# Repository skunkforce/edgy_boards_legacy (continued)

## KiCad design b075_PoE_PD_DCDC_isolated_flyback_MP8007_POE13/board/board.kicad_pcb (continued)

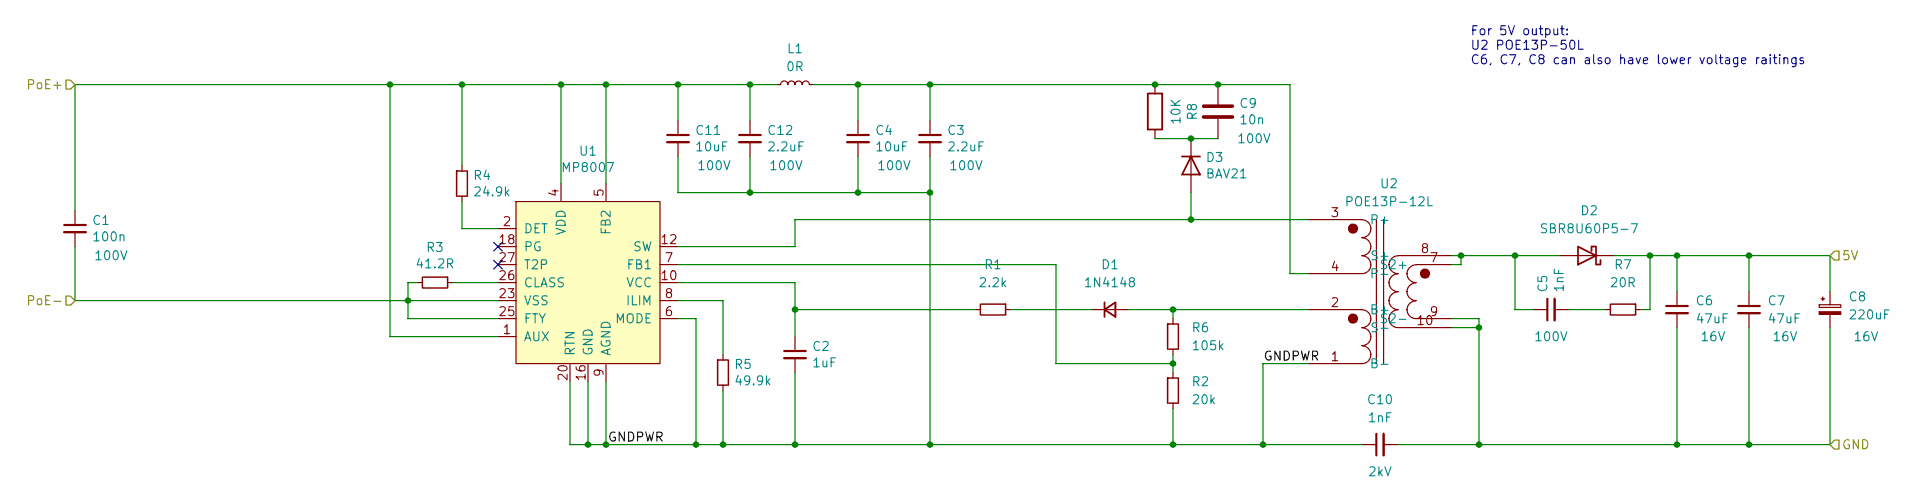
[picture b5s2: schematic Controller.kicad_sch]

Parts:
C1: 100n; C_0603_1608Metric; Voltage 100V
C2: 1uF; C_0603_1608Metric
C3, C12: 2.2uF; C_1210_3225Metric; Voltage 100V
C4, C11: 10uF; C_1210_3225Metric; Voltage 100V
C5: 1nF; C_0603_1608Metric; Voltage 100V; MPN GRM188R72A102KA01D
C6, C7: 47uF; C_1210_3225Metric; Voltage 16V
C8: 220uF; CP_Elec_10x10.5; Voltage 16V
C9: 10n; C_0805_2012Metric; Voltage 100V; MPN GRM216R72A103KA01D
C10: 1nF; C_1825_4564Metric; Voltage 2kV
D1: 1N4148; D_SOD-323; DigiKey_PN 1N4148WS_R1_00001
D2: SBR8U60P5-7; D_PowerDI-5
D3: BAV21; D_SOD-323_HandSoldering; DigiKey_PN BAV21WS_R1_00001
L1: 0R; L_1812_4532Metric
R1: 2.2k; R_0603_1608Metric
R2: 20k; R_0603_1608Metric
R3: 41.2R; R_0603_1608Metric
R4: 24.9k; R_0603_1608Metric
R5: 49.9k; R_0603_1608Metric
R6: 105k; R_0603_1608Metric
R7: 20R; R_0603_1608Metric
R8: 10K; R_1206_3216Metric
U1: MP8007; QFN-28-1EP_4x5mm_P0.5mm_EP2.65x3.65mm_ThermalVias
U2: POE13P-12L; Transformer_Coilcraft_POE13P

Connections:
/Controller/5V: C6.1, C7.1, C8.1, D2.1 (K), R7.1; also elsewhere on the board
/Controller/GNDPWR: C2.2, C3.2, C4.2, C10.1, C11.2, C12.2, R2.2, R5.2, U1.6 (MODE), U1.9 (AGND), U1.14 (NC), U1.15 (NC), U1.16 (GND), U1.17, U1.19 (NC), U1.20 (RTN), U1.21, U1.22 (NC), U1.29 (GND), U2.1 (B-)
/Controller/PoE+: C1.1, C11.1, C12.1, L1.1, R4.1, U1.1 (AUX), U1.4 (VDD), U1.5 (FB2); also elsewhere on the board
/Controller/PoE-: C1.2, R3.2, U1.23 (VSS), U1.24, U1.25 (FTY); also elsewhere on the board
GND: C6.2, C7.2, C8.2, C10.2, U2.9 (S2-), U2.10 (S-); also elsewhere on the board
unnamed: C2.1, R1.2, U1.10 (VCC)
unnamed: C3.1, C4.1, C9.1, L1.2, R8.2, U2.4 (P-)
unnamed: C5.2, R7.2
unnamed: C9.2, D3.1 (K), R8.1
unnamed: D1.1 (K), R1.1
unnamed: D1.2 (A), R6.1, U2.2 (B+)
unnamed: C5.1, D2.2 (A), U2.7 (S2+), U2.8 (S+)
unnamed: D3.2 (A), U1.12 (SW), U1.13, U2.3 (P+)
unnamed: R2.1, R6.2, U1.7 (FB1)
unnamed: R3.1, U1.26 (CLASS)
unnamed: R4.2, U1.2 (DET)
unnamed: R5.1, U1.8 (ILIM)

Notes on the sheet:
For 5V output: U2 POE13P-50L C6, C7, C8 can also have lower voltage raitings

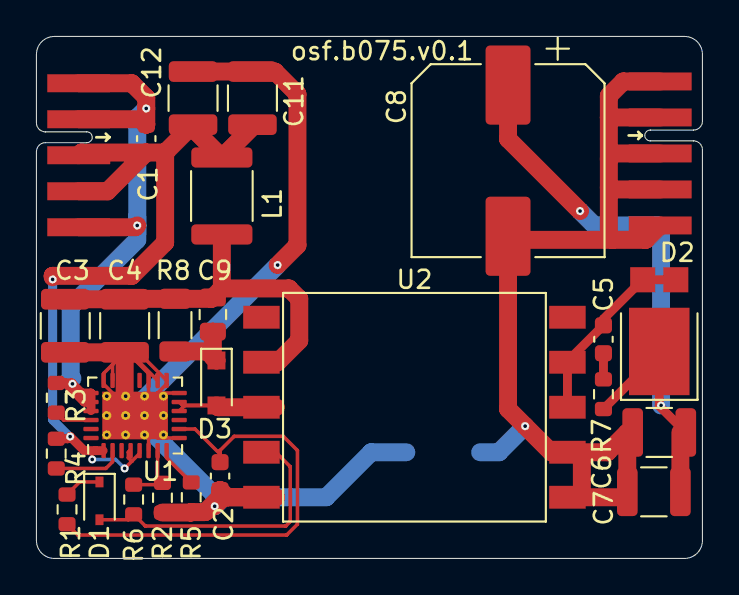
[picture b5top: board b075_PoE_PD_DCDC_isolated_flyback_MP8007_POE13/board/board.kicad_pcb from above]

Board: 2 copper layers, 37.0 x 29.0 mm, 28 parts (1 on the bottom side), 17 nets.

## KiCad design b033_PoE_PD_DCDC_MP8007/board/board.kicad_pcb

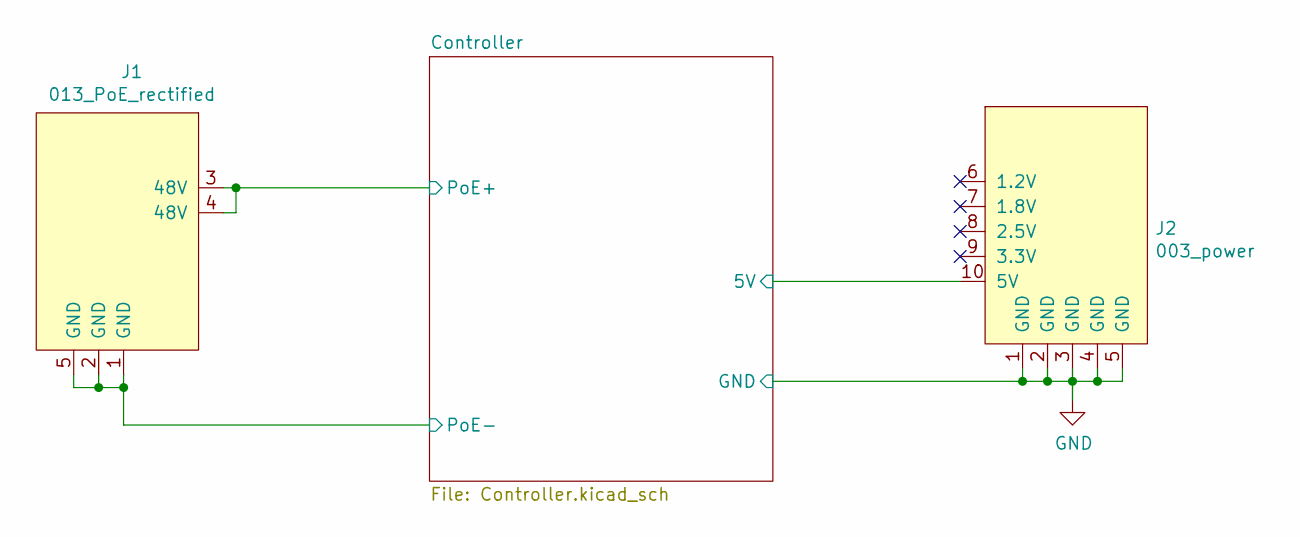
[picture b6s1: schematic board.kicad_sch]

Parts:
J1: 013_PoE_rectified; on_edge_2x05_device
J2: 003_power; on_edge_2x05_host

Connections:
/Controller/5V: J2.10 (5V); also elsewhere on the board
/Controller/PoE+: J1.3 (48V), J1.4 (48V); also elsewhere on the board
/Controller/PoE-: J1.1 (GND), J1.2 (GND), J1.5 (GND); also elsewhere on the board
GND: J2.1 (GND), J2.2 (GND), J2.3 (GND), J2.4 (GND), J2.5 (GND); also elsewhere on the board

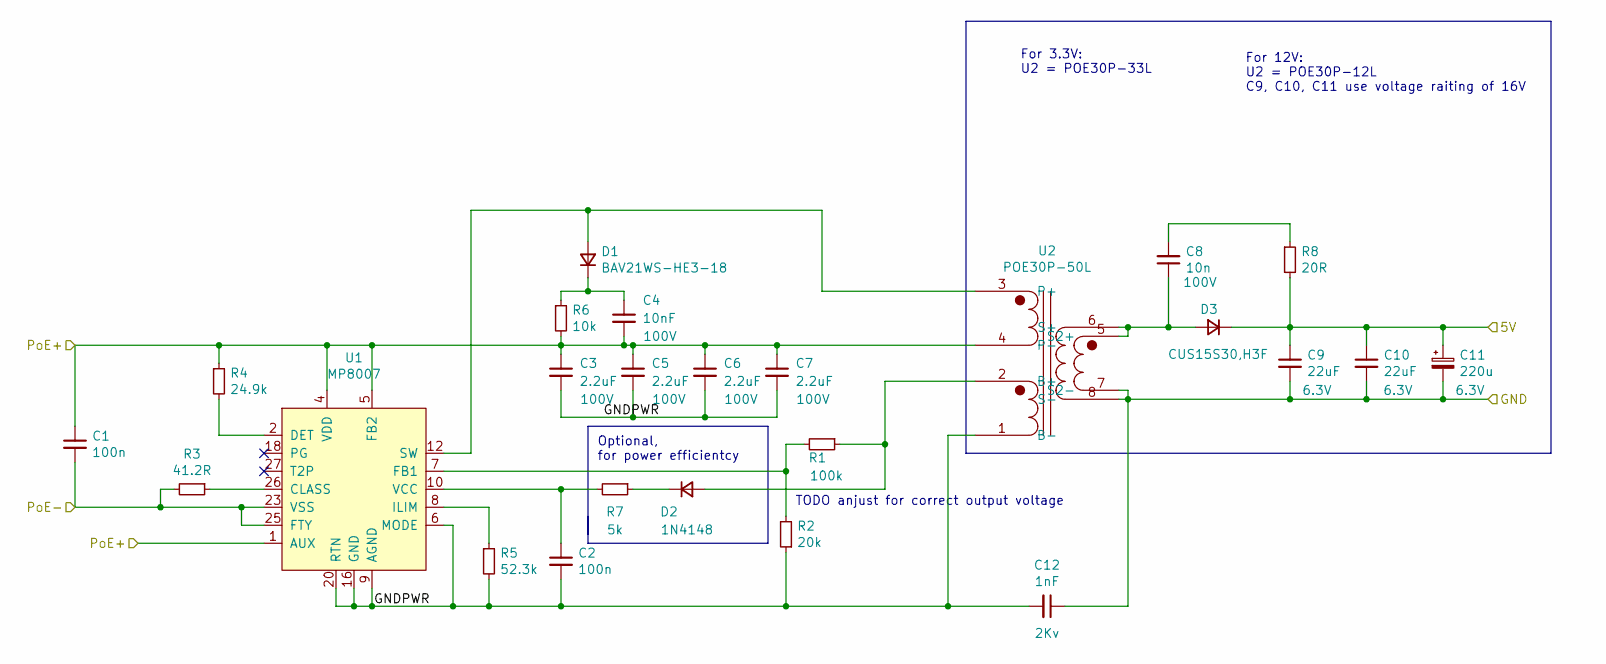
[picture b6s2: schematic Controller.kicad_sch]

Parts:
C1, C2: 100n; C_0603_1608Metric
C3, C5, C6, C7: 2.2uF; C_1210_3225Metric; Voltage 100V
C4: 10nF; C_0603_1608Metric; Voltage 100V
C8: 10n; C_0603_1608Metric; Voltage 100V
C9, C10: 22uF; C_0805_2012Metric; Voltage 6.3V
C11: 220u; CP_EIA-7343-31_Kemet-D; Voltage 6.3V
C12: 1nF; C_1806_4516Metric; Voltage 2Kv
D1: BAV21WS-HE3-18; D_SOD-323_HandSoldering
D2: 1N4148; D_SOD-323_HandSoldering
D3: CUS15S30,H3F; D_SOD-323_HandSoldering
R1: 100k; R_0603_1608Metric
R2: 20k; R_0603_1608Metric
R3: 41.2R; R_0603_1608Metric
R4: 24.9k; R_0603_1608Metric
R5: 52.3k; R_0603_1608Metric
R6: 10k; R_0603_1608Metric
R7: 5k; R_0603_1608Metric
R8: 20R; R_0603_1608Metric
U1: MP8007; QFN-28-1EP_4x5mm_P0.5mm_EP2.65x3.65mm_ThermalVias
U2: POE30P-50L; Transformer_Coilcraft_POE30P

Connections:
/Controller/5V: C9.1, C10.1, C11.1, D3.1 (K), R8.2; also elsewhere on the board
/Controller/GNDPWR: C2.2, C3.2, C5.2, C6.2, C7.2, C12.2, R2.1, R5.2, U1.6 (MODE), U1.9 (AGND), U1.16 (GND), U1.17, U1.20 (RTN), U1.21, U1.29 (GND), U2.1 (B-)
/Controller/PoE+: C1.1, C3.1, C4.2, C5.1, C6.1, C7.1, R4.1, R6.2, U1.1 (AUX), U1.4 (VDD), U1.5 (FB2), U2.4 (P-); also elsewhere on the board
/Controller/PoE-: C1.2, R3.2, U1.23 (VSS), U1.24, U1.25 (FTY); also elsewhere on the board
GND: C9.2, C10.2, C11.2, C12.1, U2.7 (S2-), U2.8 (S-); also elsewhere on the board
unnamed: C2.1, R7.2, U1.10 (VCC)
unnamed: C8.1, D3.2 (A), U2.5 (S2+), U2.6 (S+)
unnamed: C8.2, R8.1
unnamed: C4.1, D1.1 (K), R6.1
unnamed: D1.2 (A), U1.12 (SW), U1.13, U2.3 (P+)
unnamed: D2.1 (K), R7.1
unnamed: D2.2 (A), R1.1, U2.2 (B+)
unnamed: R1.2, R2.2, U1.7 (FB1)
unnamed: R4.2, U1.2 (DET)
unnamed: R5.1, U1.8 (ILIM)
unnamed: R3.1, U1.26 (CLASS)

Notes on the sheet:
For 12V: U2 = POE30P-12L C9, C10, C11 use voltage raiting of 16V
Optional, for power efficientcy
TODO anjust for correct output voltage
For 3.3V: U2 = POE30P-33L

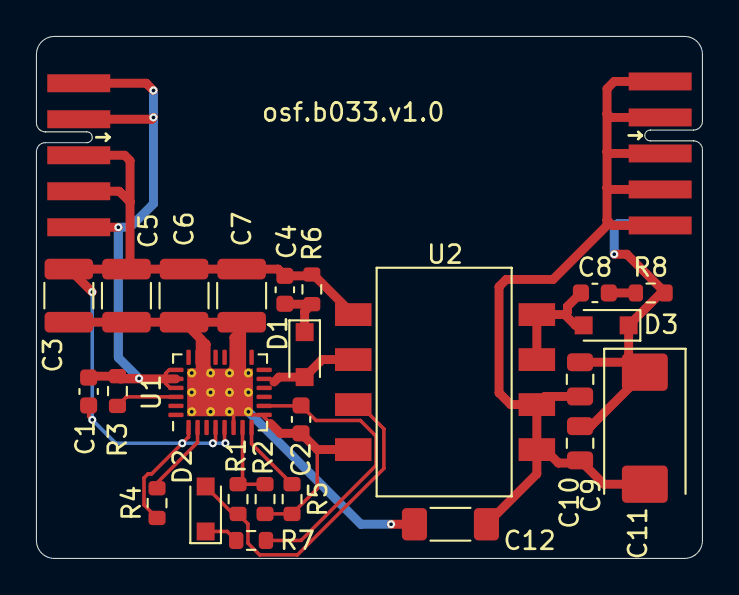
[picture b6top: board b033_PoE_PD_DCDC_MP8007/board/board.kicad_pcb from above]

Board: 2 copper layers, 37.0 x 29.0 mm, 27 parts (0 on the bottom side), 16 nets.

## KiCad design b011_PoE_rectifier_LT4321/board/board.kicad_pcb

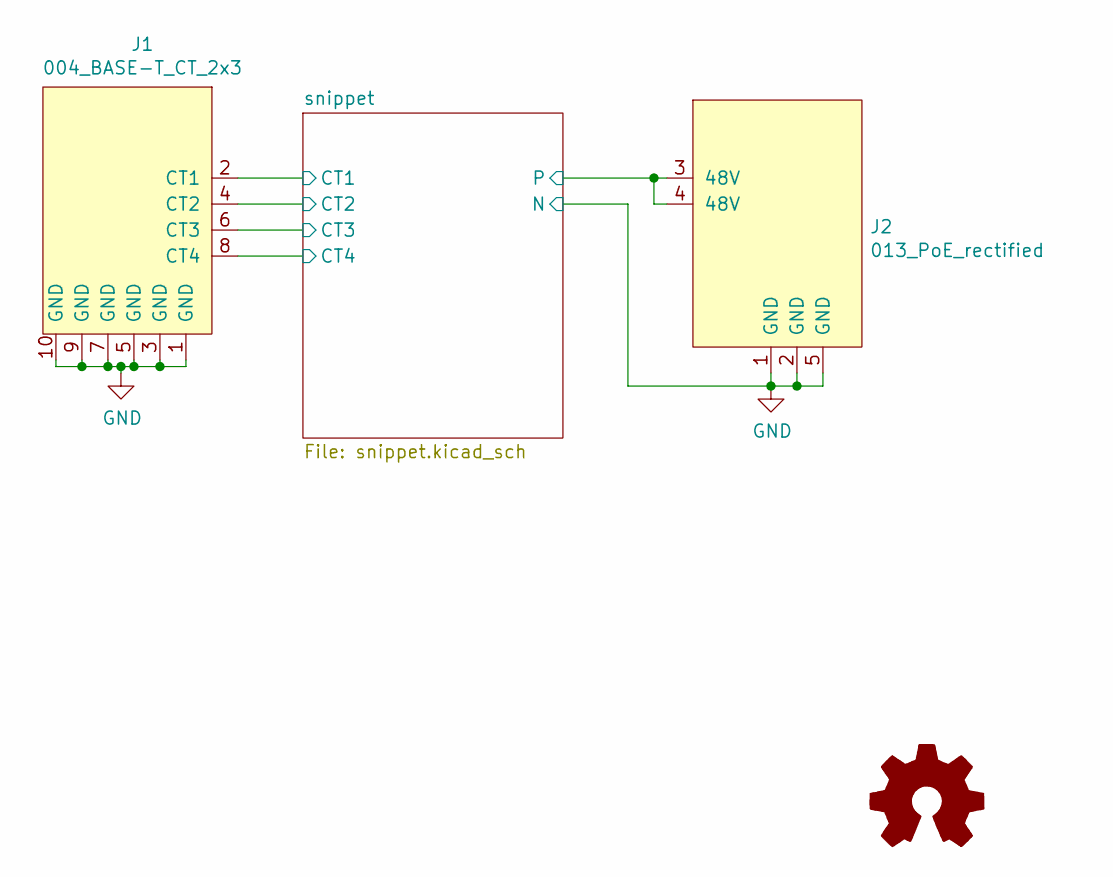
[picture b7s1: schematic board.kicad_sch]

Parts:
J1: 004_BASE-T_CT_2x3; on_edge_2x05_device
J2: 013_PoE_rectified; on_edge_2x05_host
LOGO1: Logo_Open_Hardware_Small; OSHW-Logo2_9.8x8mm_SilkScreen

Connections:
/snippet/CT_12: J1.2 (CT1); also elsewhere on the board
/snippet/CT_36: J1.4 (CT2); also elsewhere on the board
/snippet/CT_45: J1.6 (CT3); also elsewhere on the board
/snippet/CT_78: J1.8 (CT4); also elsewhere on the board
/snippet/VPORTP: J2.3 (48V), J2.4 (48V); also elsewhere on the board
GND: J1.1 (GND), J1.3 (GND), J1.5 (GND), J1.7 (GND), J1.9 (GND), J1.10 (GND), J2.1 (GND), J2.2 (GND), J2.5 (GND); also elsewhere on the board

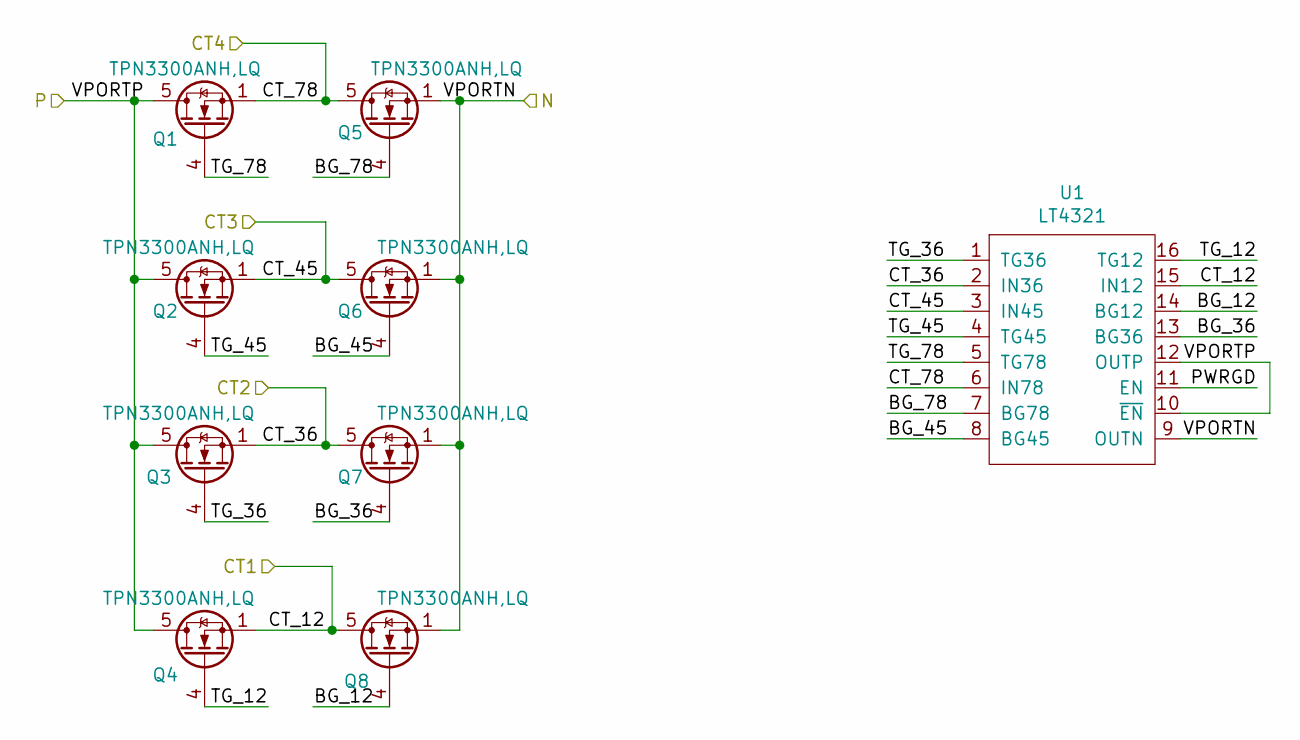
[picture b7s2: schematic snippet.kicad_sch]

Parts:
Q1, Q2, Q3, Q4, Q5, Q6, Q7, Q8: TPN3300ANH,LQ; LFPAK33; MPN TPN3300ANH,LQ
U1: LT4321; WQFN-16-1EP_4x4mm_P0.5mm_EP2.6x2.6mm; MPN LT4321IUF#PBF; Digi-Key_PN LT4321IUF#PBF-ND

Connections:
/snippet/BG_12: Q8.4 (G), U1.14 (BG12)
/snippet/BG_36: Q7.4 (G), U1.13 (BG36)
/snippet/BG_45: Q6.4 (G), U1.8 (BG45)
/snippet/BG_78: Q5.4 (G), U1.7 (BG78)
/snippet/CT_12: Q4.1 (S), Q4.2 (S), Q4.3 (S), Q8.5 (D), U1.15 (IN12); also elsewhere on the board
/snippet/CT_36: Q3.1 (S), Q3.2 (S), Q3.3 (S), Q7.5 (D), U1.2 (IN36); also elsewhere on the board
/snippet/CT_45: Q2.1 (S), Q2.2 (S), Q2.3 (S), Q6.5 (D), U1.3 (IN45); also elsewhere on the board
/snippet/CT_78: Q1.1 (S), Q1.2 (S), Q1.3 (S), Q5.5 (D), U1.6 (IN78); also elsewhere on the board
/snippet/PWRGD: U1.11 (EN)
/snippet/TG_12: Q4.4 (G), U1.16 (TG12)
/snippet/TG_36: Q3.4 (G), U1.1 (TG36)
/snippet/TG_45: Q2.4 (G), U1.4 (TG45)
/snippet/TG_78: Q1.4 (G), U1.5 (TG78)
/snippet/VPORTP: Q1.5 (D), Q2.5 (D), Q3.5 (D), Q4.5 (D), U1.10 (~EN), U1.12 (OUTP); also elsewhere on the board
GND: Q5.1 (S), Q5.2 (S), Q5.3 (S), Q6.1 (S), Q6.2 (S), Q6.3 (S), Q7.1 (S), Q7.2 (S), Q7.3 (S), Q8.1 (S), Q8.2 (S), Q8.3 (S), U1.9 (OUTN), U1.17 (EP); also elsewhere on the board

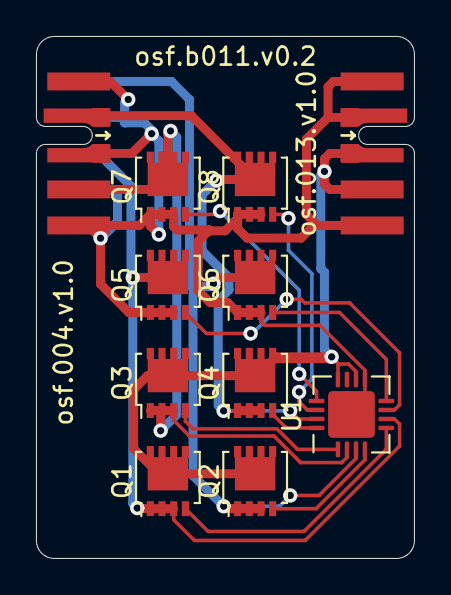
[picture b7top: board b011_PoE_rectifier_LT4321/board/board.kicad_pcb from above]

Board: 2 copper layers, 21.0 x 29.0 mm, 12 parts (1 on the bottom side), 14 nets.

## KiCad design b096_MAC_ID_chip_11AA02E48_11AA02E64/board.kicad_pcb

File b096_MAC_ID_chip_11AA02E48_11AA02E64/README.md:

# MAC ID chip

## difference between a MAC and EUI-48
The subtle difference between EUI-48 and MAC-48 was not well understood; as a result, the term MAC-48 is now obsolete and the term EUI-48 is used for both (but the terms “MAC” and “MAC address” are still used).

In other words, EUI-48 and the MAC number of a device represent the same thing! Usually it is represented in 12 hex (e.g. 0023.a34e.abc9), equivalent to 48 bits or 6 bytes.

## connectability
Most microcontroller boards are not going to have a osf.B021 connector. This connector is however compatible with SPI, I2C, GPIO and many others. 

## tests
untested.

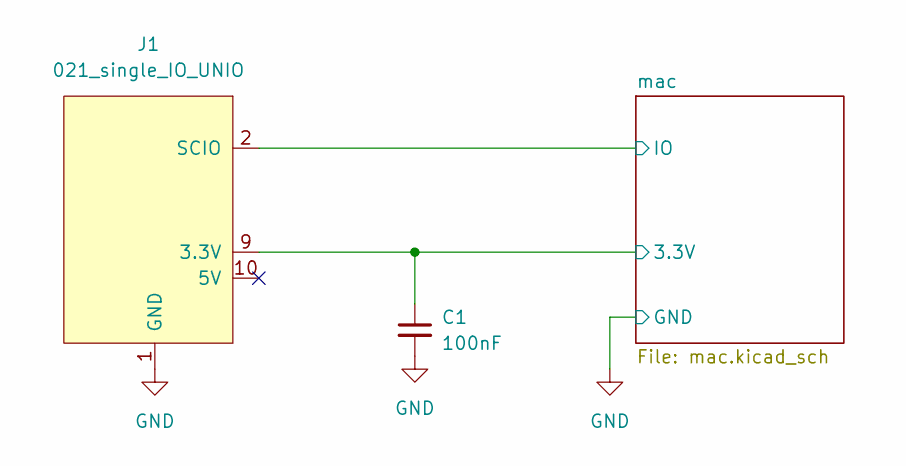
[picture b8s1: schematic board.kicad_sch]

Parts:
C1: 100nF; C_0603_1608Metric
J1: 021_single_IO_UNIO; on_edge_2x05_device

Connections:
/mac/3.3V: C1.1, J1.9 (3.3V); also elsewhere on the board
/mac/IO: J1.2 (SCIO); also elsewhere on the board
GND: C1.2, J1.1 (GND); also elsewhere on the board

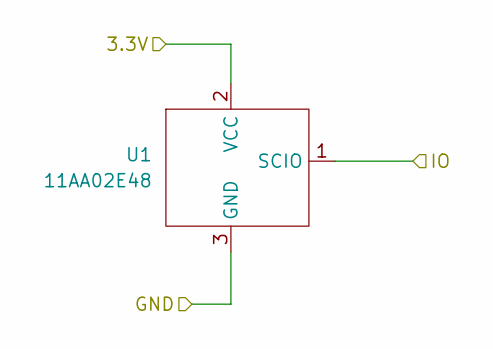
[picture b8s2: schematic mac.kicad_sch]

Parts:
U1: 11AA02E48; SOT-23

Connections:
/mac/3.3V: U1.2 (VCC); also elsewhere on the board
/mac/IO: U1.1 (SCIO); also elsewhere on the board
GND: U1.3 (GND); also elsewhere on the board

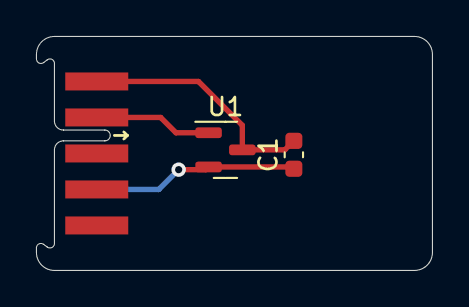
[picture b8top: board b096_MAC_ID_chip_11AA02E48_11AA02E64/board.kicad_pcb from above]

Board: 4 copper layers, 22.0 x 13.0 mm, 3 parts (0 on the bottom side), 3 nets.

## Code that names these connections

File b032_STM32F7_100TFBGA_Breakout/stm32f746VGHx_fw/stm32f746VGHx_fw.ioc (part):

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Mcu.Name=STM32F746V(E-G)Hx
Mcu.Package=TFBGA100
Mcu.UserName=STM32F746VGHx
PA0/WKUP.Signal=ADCx_IN0
PA1.Mode=RMII
PA1.Signal=ETH_REF_CLK
PA11.Mode=Device_Only
PA11.Signal=USB_OTG_FS_DM
PA12.Mode=Device_Only
PA12.Signal=USB_OTG_FS_DP
PA13.Signal=SYS_JTMS-SWDIO
PA14.Signal=SYS_JTCK-SWCLK
PA15.Mode=NSS_Signal_Hard_Output
PA15.Signal=SPI1_NSS
PA2.Mode=RMII
PA2.Signal=ETH_MDIO
PA3.Signal=ADCx_IN3
PA4.Signal=ADCx_IN4
PA5.Signal=ADCx_IN5
PA6.Signal=ADCx_IN6
PA7.Mode=RMII
PA7.Signal=ETH_CRS_DV
PA8.Mode=I2C
PA8.Signal=I2C3_SCL
PB0.Signal=ADCx_IN8
PB1.Signal=ADCx_IN9
PB10.Mode=Full_Duplex_Master
PB10.Signal=SPI2_SCK
PB11.Mode=RMII
PB11.Signal=ETH_TX_EN
PB12.Mode=RMII
PB12.Signal=ETH_TXD0
PB13.Mode=RMII
PB13.Signal=ETH_TXD1
PB3.Mode=Full_Duplex_Master
PB3.Signal=SPI1_SCK
PB4.Mode=Full_Duplex_Master
PB4.Signal=SPI1_MISO
PB5.Mode=Full_Duplex_Master
PB5.Signal=SPI1_MOSI
PB6.Mode=I2C
PB6.Signal=I2C1_SCL
PB7.Mode=I2C
PB7.Signal=I2C1_SDA
PB9.Mode=NSS_Signal_Hard_Output
PB9.Signal=SPI2_NSS
PC0.Signal=ADCx_IN10
PC1.Mode=RMII
PC1.Signal=ETH_MDC
PC10.Mode=Asynchronous
PC10.Signal=USART3_TX
PC11.Mode=Asynchronous
PC11.Signal=USART3_RX
PC14/OSC32_IN.Mode=LSE-External-Oscillator
PC14/OSC32_IN.Signal=RCC_OSC32_IN
PC15/OSC32_OUT.Mode=LSE-External-Oscillator
PC15/OSC32_OUT.Signal=RCC_OSC32_OUT
PC2.Mode=Full_Duplex_Master
PC2.Signal=SPI2_MISO
PC3.Mode=Full_Duplex_Master
PC3.Signal=SPI2_MOSI
PC4.Mode=RMII
PC4.Signal=ETH_RXD0
PC5.Mode=RMII
PC5.Signal=ETH_RXD1
PC9.Mode=I2C
PC9.Signal=I2C3_SDA
PD0.Mode=CAN_Activate
PD0.Signal=CAN1_RX
PD1.Mode=CAN_Activate
PD1.Signal=CAN1_TX
PD12.Mode=I2C
PD12.Signal=I2C4_SCL
PD13.Mode=I2C
PD13.Signal=I2C4_SDA
PD5.Mode=Asynchronous
PD5.Signal=USART2_TX
PD6.Mode=Asynchronous
PD6.Signal=USART2_RX
PH0/OSC_IN.Mode=HSE-External-Oscillator
PH0/OSC_IN.Signal=RCC_OSC_IN
PH1/OSC_OUT.Mode=HSE-External-Oscillator
PH1/OSC_OUT.Signal=RCC_OSC_OUT
RCC.HSE_VALUE=25000000
board=custom

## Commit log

2021-02-26 added common library symbols
2021-02-26 added connecto through boards
2021-02-26 added device to pin sockets board
2021-02-27 added ethernet phys LAN8742A and KSZ8081RND
2021-02-27 added usb hub
2021-02-27 added ethernet magnetics
2021-02-27 added usb FT2232 to debug edge
2021-02-27 added usb to ethernet
2021-02-27 added analog devices
2021-02-27 added poe rectifiers
2021-02-27 added ethernet connector
2021-02-27 added raspberri pi pico
2021-02-27 added STM32F745 breakout to I2C and ethernet
2021-03-03 added I2C device to USB
2021-03-03 added STM32F723IE with 16x ADC
2021-03-03 added part info for silicon parts
2021-03-19 added MCP4728 4x I2C DAC
2021-03-19 added usbc to power connector
2021-03-19 improved labeling
2021-04-16 changed b013 to use 3.3v as IO voltage and fixed supply voltage bug
2021-04-20 updated b004 to use version 0.2 connectors
2021-04-21 fixed connectors and power bug
2021-04-21 modernized connectors
2021-04-22 STM32F767 initial
2021-04-22 changed b007 to new plugs and 0603 as smalles component size
2021-04-22 updated ADC connector
2021-04-22 updated connectors
2021-04-22 added slave UART, new connectors and a debug port
2021-04-24 added PoE controller
2021-04-24 added simple I2C host
2021-04-25 added STM32F750 breakout
2021-04-26 power and ground changed to higherarchial labels in subsheets
2021-05-06 added ADS8688
2021-05-06 updated gitignore to ignore rescue files
2021-05-06 changes b031 to 2 layer
2021-05-11 changed connector to include 100BASE-T center taps
2021-05-13 added gnd resistors
2021-05-13 changed name to 144pin tqfp because many chips are compatible with the board
2021-05-13 add 100TQFP
2021-05-13 added 100TFBGA
2021-05-13 updated usb plugs
2021-05-13 updated ethernet connector
2021-05-13 improved b008 but not done
2021-05-13 updated plugs
2021-05-13 changed to horizontal style
2021-05-13 fixed ground bugs
2021-05-13 ordered version
2021-05-21 updated to use new connectors and better form factor
2021-05-21 added stub connector for up and down connections
2021-05-21 added MP8007
2021-05-21 added 1 wire conponents
2021-05-22 added sloppy test of cm4, will update if it works
2021-05-22 added 5 port switch
2021-05-28 added stm32f042 breakout
2021-05-28 added mic preamp
2021-05-28 added poe pse breakout
2021-05-28 added i2c isolator
2021-05-28 added usbc connector
2021-06-04 modified to use USB edge connector
2021-06-08 updated folder name because the part supports 100base-t not 1000base-t
2021-06-08 renamed incorrectly named part
2021-06-08 moved identifier to be printed on board correctly
2021-06-08 added non isolated version of MP8007
2021-08-05 added open hardware logo
2021-08-05 added OSHW logo and updated usb connector version in schemetic
2021-08-05 added b060
2021-08-05 corrected pinout of b010
2021-08-10 added b003 jumber pss through
2021-08-12 added pi breakout, 5v isolator and spi isolator
2021-08-13 added ADUM5401
2021-08-13 added ADUM5411
2021-08-17 updated pico board to use the rp2040
2021-10-11 cleaned up silkscreen
2021-10-11 fixed lib path issue
2021-10-11 fixed lib path issues
2021-11-08 corrected silkscreen
2021-11-10 updated gitignore
2021-11-10 initial b065 CANFD Controller
2021-11-10 initial b066 CANFD transceiver
2021-11-10 added more comprihensive board descriptions to readme
2021-11-10 initial b063
2021-11-10 initial b001 stub connector
2021-11-10 initial b002
2021-11-10 initial b003
2021-11-10 initial b004
2021-11-10 added opean hardware logo
2021-11-10 initial b008
2021-11-10 added propper path to put_on_edge
2021-11-11 version 3
2021-11-11 cleaned up symbol lib paths
2021-11-11 version 0.3 with ADS868xIRUM with TSSOP footprint
2021-11-11 changed to use the rpi2040 directly rather than the pi pico
2021-11-13 initial b067
2021-11-18 initial b068
2021-11-30 added quarz part number ABM8G-12.000MHZ-4Y-T3
2021-11-30 moved b013 to new branch
2021-11-30 initial b070
2021-12-02 changed mosfet for availability
2021-12-02 b027 initial
2021-12-02 initial b029
2021-12-02 added PoE++ boards
2021-12-06 updated analog connector footprint
2021-12-06 b051 initial
2021-12-06 changed debug footprint to debug edge
2021-12-07 added b012
2021-12-07 added workflow diagramm to README.md
2021-12-08 b002 LDO hinzugefügt
2021-12-12 initial b061
2021-12-12 initial b062 SPI isolator
2021-12-12 removed duplicated footprints and symbols from put_on_edge
2021-12-15 initial b071
2021-12-18 initial b072 quad spi flash
2022-01-31 b073 initial
2022-02-21 b078 initial
2022-02-24 initial b079 SD card to SPI
2022-02-24 converted to kicad 6
2022-02-24 initial b077 PoE DCDC
2022-03-03 updated to kicad 6
2022-03-03 modernized to kicad 6
2022-03-03 initial b001 stub connector (#24)
    * initial b001 stub connector
    * modernized to kicad 6
2022-03-03 initial b003 (#26)
    * initial b003
    * modernized to kicad 6
2022-03-03 migrated to kicad 6 and resolved part library issues
2022-03-03 initial b004 (#27)
    * initial b004
    * migrated to kicad 6 and resolved part library issues
2022-03-03 initial b005 ethernet to 020 100BASE-T
2022-03-03 initial b007 LAN8742A phy
2022-03-03 updated to keycad 6, new MII connector
2022-03-03 initial b009 ethernet with magnetics
2022-03-04 updated to kicad 6 (#54)
2022-03-04 b046 initial
2022-03-04 added support for different bus addresses
2022-03-04 added test results to b063
2022-03-07 updated to kicad 6, potential pinning issues remain
2022-03-07 connected int and status lines, now version 1.0
2022-03-07 updated quarz to 40mhz
2022-03-07 initial b053 STM32F107 breakout
2022-03-07 removed b016 from main because its not done and therefore should not be in main. Its in its own branch oh/b016 for now untill its finished
2022-03-07 b016 initial
2022-03-07 modernized to kicad 6 and added missing LDO
2022-03-08 Schaltplan b080 erstellt
2022-03-10 "Reset pull-up, INT pin conn, change crystal fp"
    Added 10k pull ups to all reset Pins, connected pin 15 of the stm to int
    pin of spi connector, changed footprint for crystal to bigger one so
    that 48MHz crystal would also fit
2022-03-10 add STM32G030 to local parts lib
2022-03-10 started routing
2022-03-11 finished routing v0.1
2022-03-13 fixed missing connections mentioned in PR #64. cleaned up lib connections and bumped version to 1.0
2022-03-14 cleaned up unneeded symbols and footprints
2022-03-14 initial b081
2022-03-14 added different power variants
2022-03-14 initial b083
2022-03-14 rearranged components for better layout
2022-03-15 added flash chip to QSPI interface
2022-03-17 initial b085
2022-03-17 initial b084
2022-03-17 added EEPROM, modernized connectors. still needs LDO
2022-03-17 added LDO
2022-03-17 reorganized components so that silk screen has room
2022-03-17 added b016 and b017
2022-03-17 b019 initial
2022-03-17 added b018 and b019
2022-03-17 initial b022
2022-03-17 b021 initial
2022-03-20 added b021 and b022
2022-03-21 initial b086
2022-03-21 added b023 and b024
2022-03-22 added b025
2022-03-22 added more
2022-03-22 upgraded to new kicad6
2022-03-22 added b031
2022-03-22 added b033
2022-03-22 added b034
2022-03-23 initial b076
2022-03-23 added b087
2022-03-23 initial b087
2022-03-23 added b036, b043 and b044
2022-03-23 added unfinished boards from the old dev branch
2022-03-23 initial b056
2022-03-23 added b056
2022-03-24 added b059
2022-03-24 fixed typo
2022-03-24 initial b082
2022-03-24 fixed kicad_prl exclusion
2022-03-24 initial b049
2022-03-26 added link to product in readme
2022-03-31 added missing boards to readme
2022-03-31 added DCDC descriptions
2022-04-01 updated crystal
2022-04-02 initial b088
2022-04-02 added b088 and b089
2022-04-02 initial b089
2022-04-02 added b090
2022-04-03 initial b090
2022-04-04 updated diode to show part number SDT10A45P5-13D
2022-04-05 added b091
2022-04-07 board.kicad_prl should not be tracked as it holds local settings
2022-04-07 initial b091
2022-04-07 added host side pull ups for I2C
2022-04-07 updated to narrower edge connectors
2022-04-07 added pullups for I2C, fixed rp2040 footprint and modernized to use narrower sloted connectors
2022-04-07 added I2C pull ups, changed debug connector footprint, modernized to skinny slot connectors
2022-04-07 updated status
2022-04-09 Update Symbol and relayout b076 dcdc
2022-04-09 Update edge connectors
    reroute a little bit
2022-04-11 Update Silkscreen
2022-04-11 dev board cloned
2022-04-11 Fix supply, better thermal mgmt.
2022-04-11 Update PWR fix
2022-04-11 Update Silk
2022-04-12 b078 tested
2022-04-12 b078 W5500 SPI to Ethernet Phy and MAC (#49)
    * b078 initial
    * added link to product in readme
    * updated crystal
2022-07-11 b056v0.2: Footprint von ads geändert zu qfn 4x4
2022-07-14 silkscreen auf v0.2 angepasst
2022-08-12 Update README.md
    added b092 TMCS110
2022-08-12 Add initial version of tmcs1100 power edgy
2022-08-12 Update ref. voltage connections and fix via sizes
2022-08-17 b052 initial
2022-08-17 added b093 PoE DCDC flyback to README
2022-08-18 b093 initial
2022-08-18 added silkscreen, bigger gap between input
2022-10-26 initial commit, symbol
2022-11-18 added b093 with USB2517
2022-11-18 fixed clash with b093
2022-11-21 initial b094
2022-12-16 added SOM connector layout
2022-12-22 version 0.3
2022-12-22 version 0.1
2022-12-23 added strapping and quartz resistors
2022-12-23 increased board size and updated component values
2023-01-11 added b095
2023-01-11 b095 initial
2023-01-13 changed socket to fit a wire to board ribbon cable
2023-01-16 updated to use new connector with thinner slot
2023-01-20 adde b096 and b097
2023-01-20 b096 initial
2023-01-20 added exact part number
2023-01-20 updated b078 status
2023-01-20 added test info
2023-01-21 improved component constraints
2023-01-23 reorganized MP8007 based designs
2023-01-23 changed coil to POE30P
2023-01-23 b075 initial
2023-01-24 b074 initial
2023-01-29 added b098
2023-01-29 b098 initial
2023-02-01 added the rest of the MII interfaces
2023-02-10 fixed README
